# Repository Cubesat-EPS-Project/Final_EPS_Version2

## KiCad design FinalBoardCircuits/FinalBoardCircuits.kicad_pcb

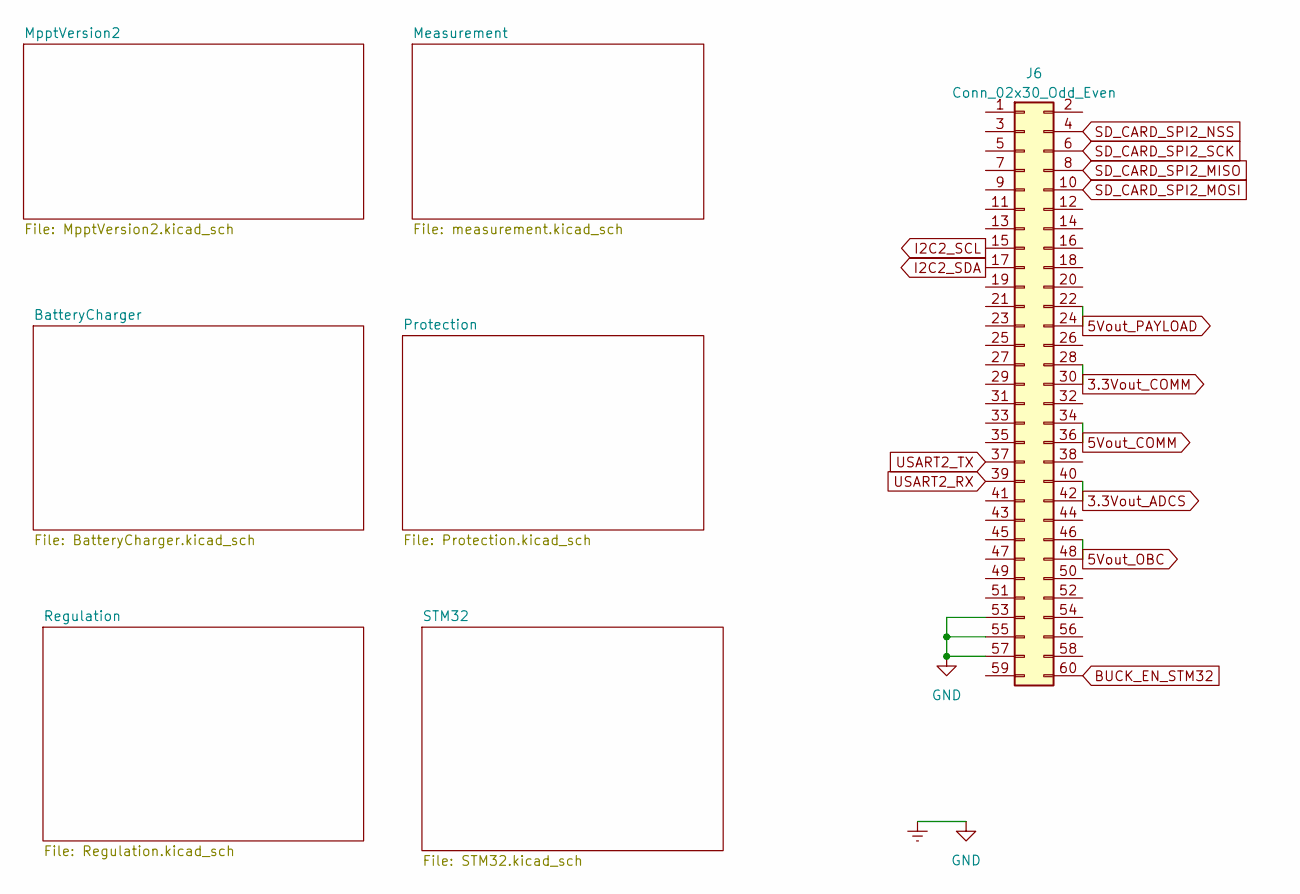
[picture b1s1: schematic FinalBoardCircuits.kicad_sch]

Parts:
J6: Conn_02x30_Odd_Even; PinSocket_2x30_P2.54mm_Vertical

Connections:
3.3Vout_ADCS: J6.40, J6.42; also elsewhere on the board
3.3Vout_COMM: J6.28, J6.30; also elsewhere on the board
5Vout_COMM: J6.34, J6.36; also elsewhere on the board
5Vout_OBC: J6.46, J6.48; also elsewhere on the board
5Vout_PAYLOAD: J6.22, J6.24; also elsewhere on the board
BUCK_EN_STM32: J6.60; also elsewhere on the board
I2C2_SCL: J6.15; also elsewhere on the board
I2C2_SDA: J6.17; also elsewhere on the board
SD_CARD_SPI2_MISO: J6.8; also elsewhere on the board
SD_CARD_SPI2_MOSI: J6.10; also elsewhere on the board
SD_CARD_SPI2_NSS: J6.4; also elsewhere on the board
SD_CARD_SPI2_SCK: J6.6; also elsewhere on the board
USART2_RX: J6.39; also elsewhere on the board
USART2_TX: J6.37; also elsewhere on the board

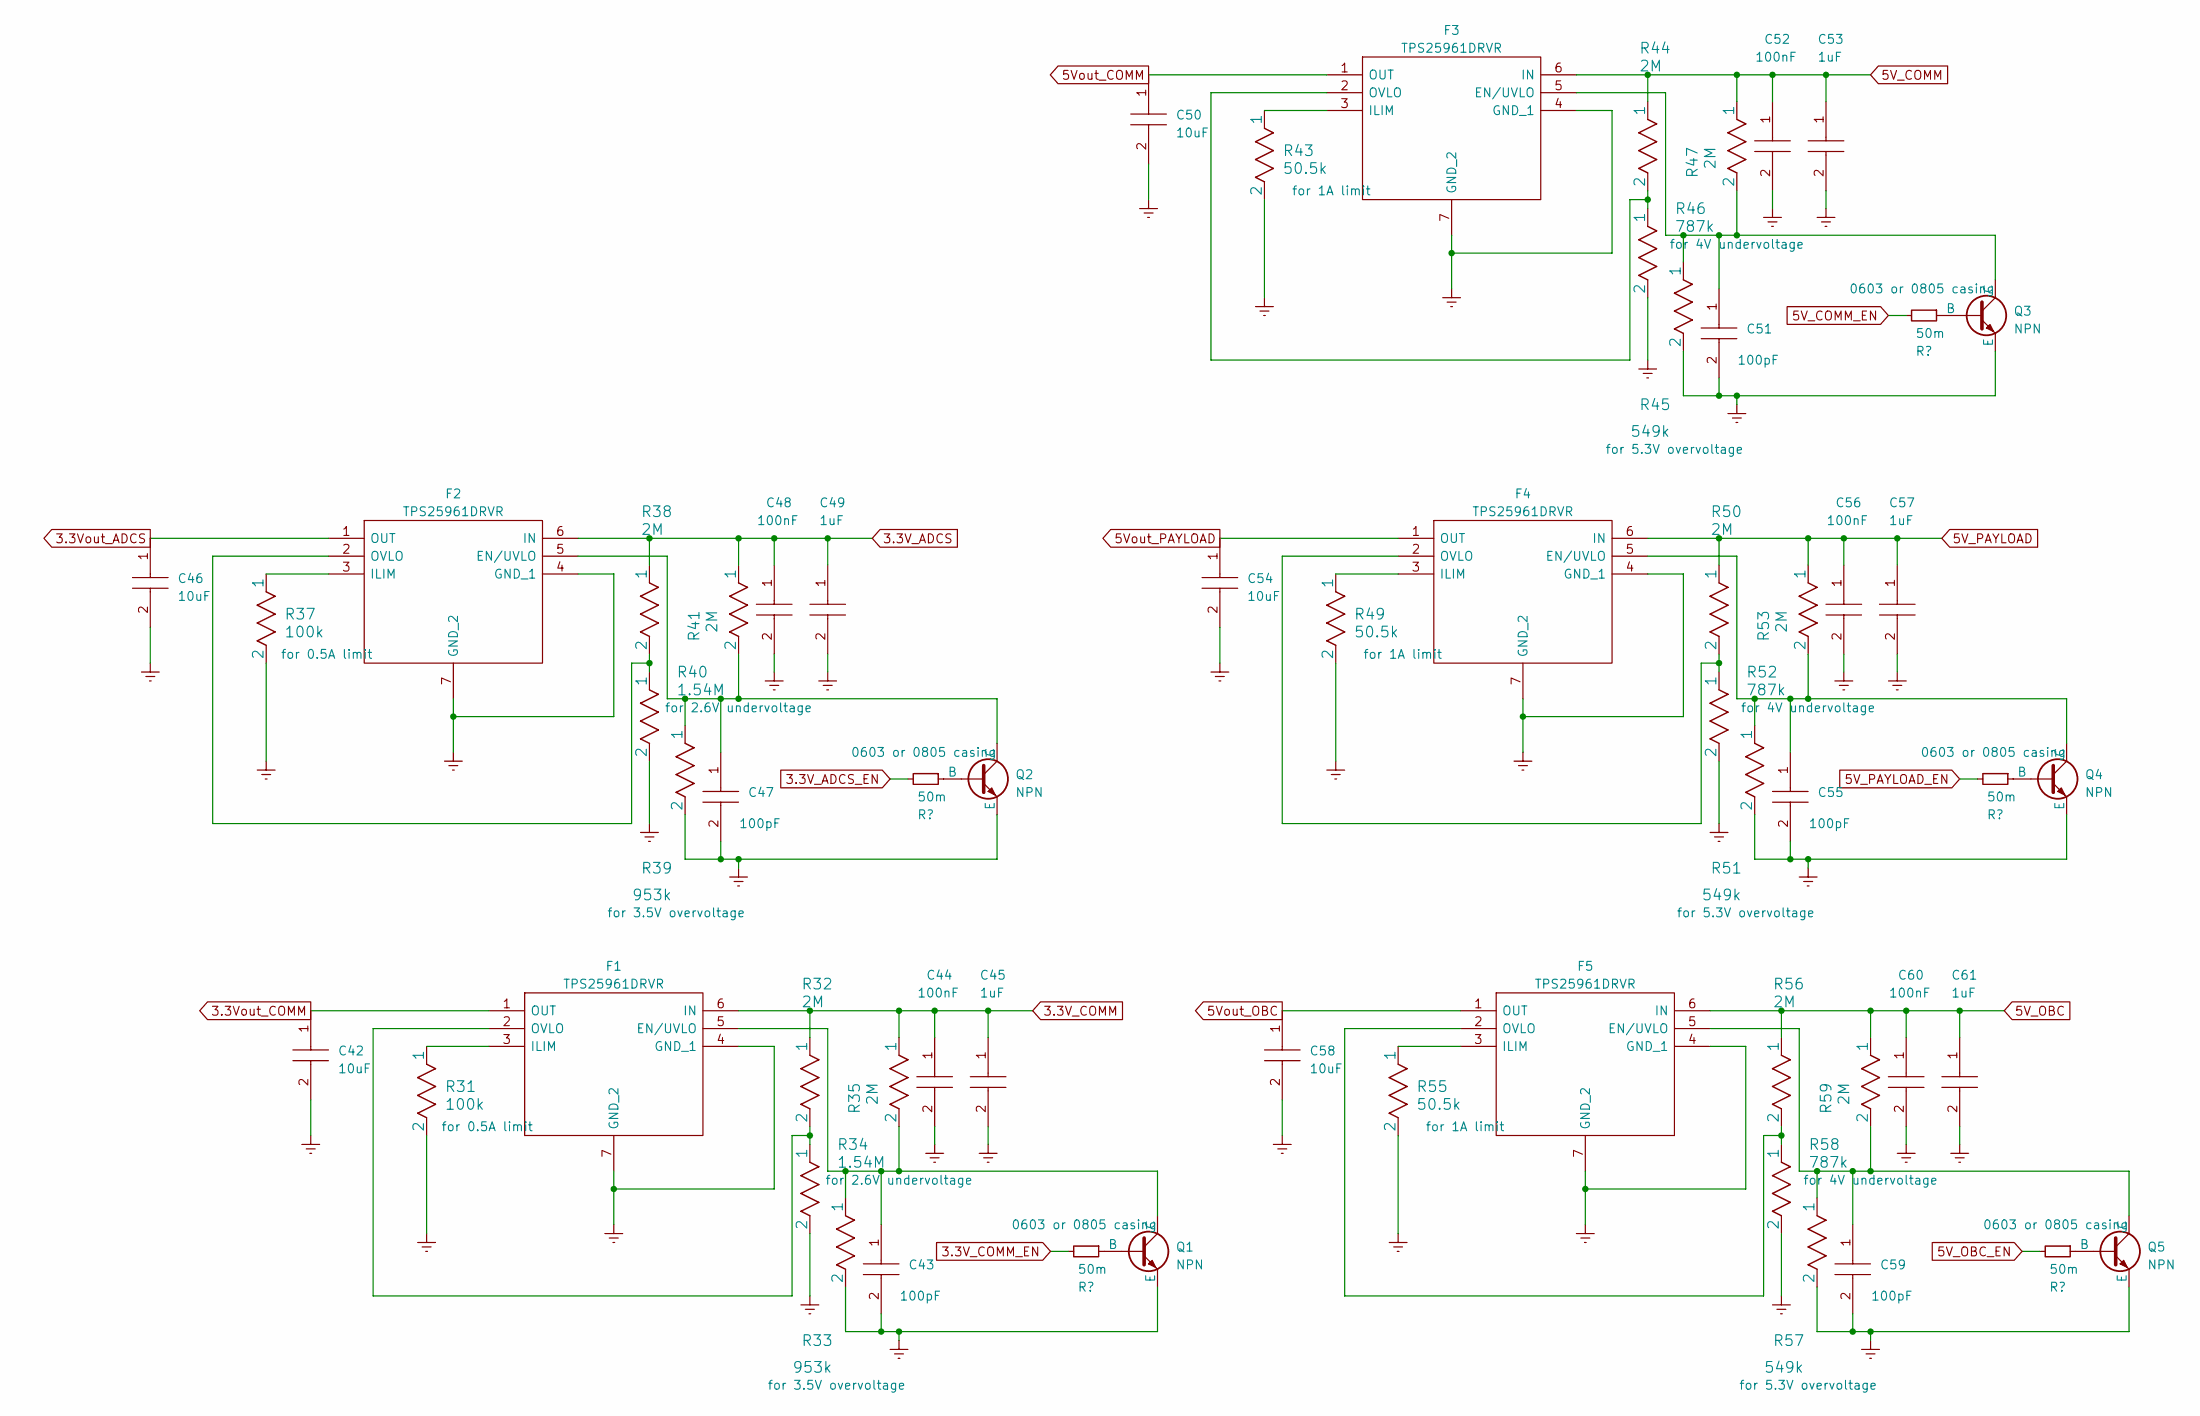
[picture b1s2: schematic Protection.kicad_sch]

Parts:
C42, C46, C50, C54, C58: 10uF; C_0805_2012Metric_Pad1.18x1.45mm_HandSolder; Mouser Part Number 581-0805YC106KAT2A
C43, C47, C51, C55, C59: 100pF; C_0805_2012Metric_Pad1.18x1.45mm_HandSolder; Mouser Part Number 80-C0402C101K3RAUTO
C44, C48, C52, C56, C60: 100nF; C_0805_2012Metric_Pad1.18x1.45mm_HandSolder; Mouser Part Number 810-C1005X7R1C104K
C45, C49, C53, C57, C61: 1uF; C_0805_2012Metric_Pad1.18x1.45mm_HandSolder; Mouser Part Number 80-C2220X105K2RAUTO
F1, F2, F3, F4, F5: TPS25961DRVR; SON65P200X200X80-7N; Mouser Part Number 595-TPS25961DRVR
Q1, Q2, Q3, Q4, Q5: NPN; PBSS4310PASQX
R31, R37: 100k; R_0805_2012Metric_Pad1.20x1.40mm_HandSolder
R32, R35, R38, R41, R44, R47, R50, R53, R56, R59: 2M; R_0805_2012Metric_Pad1.20x1.40mm_HandSolder
R33, R39: 953k; R_0805_2012Metric_Pad1.20x1.40mm_HandSolder
R34, R40: 1.54M; R_0805_2012Metric_Pad1.20x1.40mm_HandSolder
R36, R42, R48, R54, R60: 50m; R_0805_2012Metric_Pad1.20x1.40mm_HandSolder
R43, R49, R55: 50.5k; R_0805_2012Metric_Pad1.20x1.40mm_HandSolder
R45, R51, R57: 549k; R_0805_2012Metric_Pad1.20x1.40mm_HandSolder
R46, R52, R58: 787k; R_0805_2012Metric_Pad1.20x1.40mm_HandSolder

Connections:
3.3V_ADCS: C48.1, C49.1, F2.6 (IN), R38.1, R41.1; also elsewhere on the board
3.3V_ADCS_EN: R42.2; also elsewhere on the board
3.3V_COMM: C44.1, C45.1, F1.6 (IN), R32.1, R35.1; also elsewhere on the board
3.3V_COMM_EN: R36.2; also elsewhere on the board
3.3Vout_ADCS: C46.1, F2.1 (OUT); also elsewhere on the board
3.3Vout_COMM: C42.1, F1.1 (OUT); also elsewhere on the board
5V_COMM: C52.1, C53.1, F3.6 (IN), R44.1, R47.1; also elsewhere on the board
5V_COMM_EN: R48.2; also elsewhere on the board
5V_OBC: C60.1, C61.1, F5.6 (IN), R56.1, R59.1; also elsewhere on the board
5V_OBC_EN: R60.2; also elsewhere on the board
5V_PAYLOAD: C56.1, C57.1, F4.6 (IN), R50.1, R53.1; also elsewhere on the board
5V_PAYLOAD_EN: R54.2; also elsewhere on the board
5Vout_COMM: C50.1, F3.1 (OUT); also elsewhere on the board
5Vout_OBC: C58.1, F5.1 (OUT); also elsewhere on the board
5Vout_PAYLOAD: C54.1, F4.1 (OUT); also elsewhere on the board
unnamed: C43.1, F1.5 (EN/UVLO), Q1.1 (C), R34.1, R35.2
unnamed: F1.3 (ILIM), R31.1
unnamed: F1.2 (OVLO), R32.2, R33.1
unnamed: C47.1, F2.5 (EN/UVLO), Q2.1 (C), R40.1, R41.2
unnamed: F2.3 (ILIM), R37.1
unnamed: F2.2 (OVLO), R38.2, R39.1
unnamed: C51.1, F3.5 (EN/UVLO), Q3.1 (C), R46.1, R47.2
unnamed: F3.3 (ILIM), R43.1
unnamed: F3.2 (OVLO), R44.2, R45.1
unnamed: C55.1, F4.5 (EN/UVLO), Q4.1 (C), R52.1, R53.2
unnamed: F4.3 (ILIM), R49.1
unnamed: F4.2 (OVLO), R50.2, R51.1
unnamed: C59.1, F5.5 (EN/UVLO), Q5.1 (C), R58.1, R59.2
unnamed: F5.3 (ILIM), R55.1
unnamed: F5.2 (OVLO), R56.2, R57.1
unnamed: Q1.2 (B), R36.1
unnamed: Q2.2 (B), R42.1
unnamed: Q3.2 (B), R48.1
unnamed: Q4.2 (B), R54.1
unnamed: Q5.2 (B), R60.1

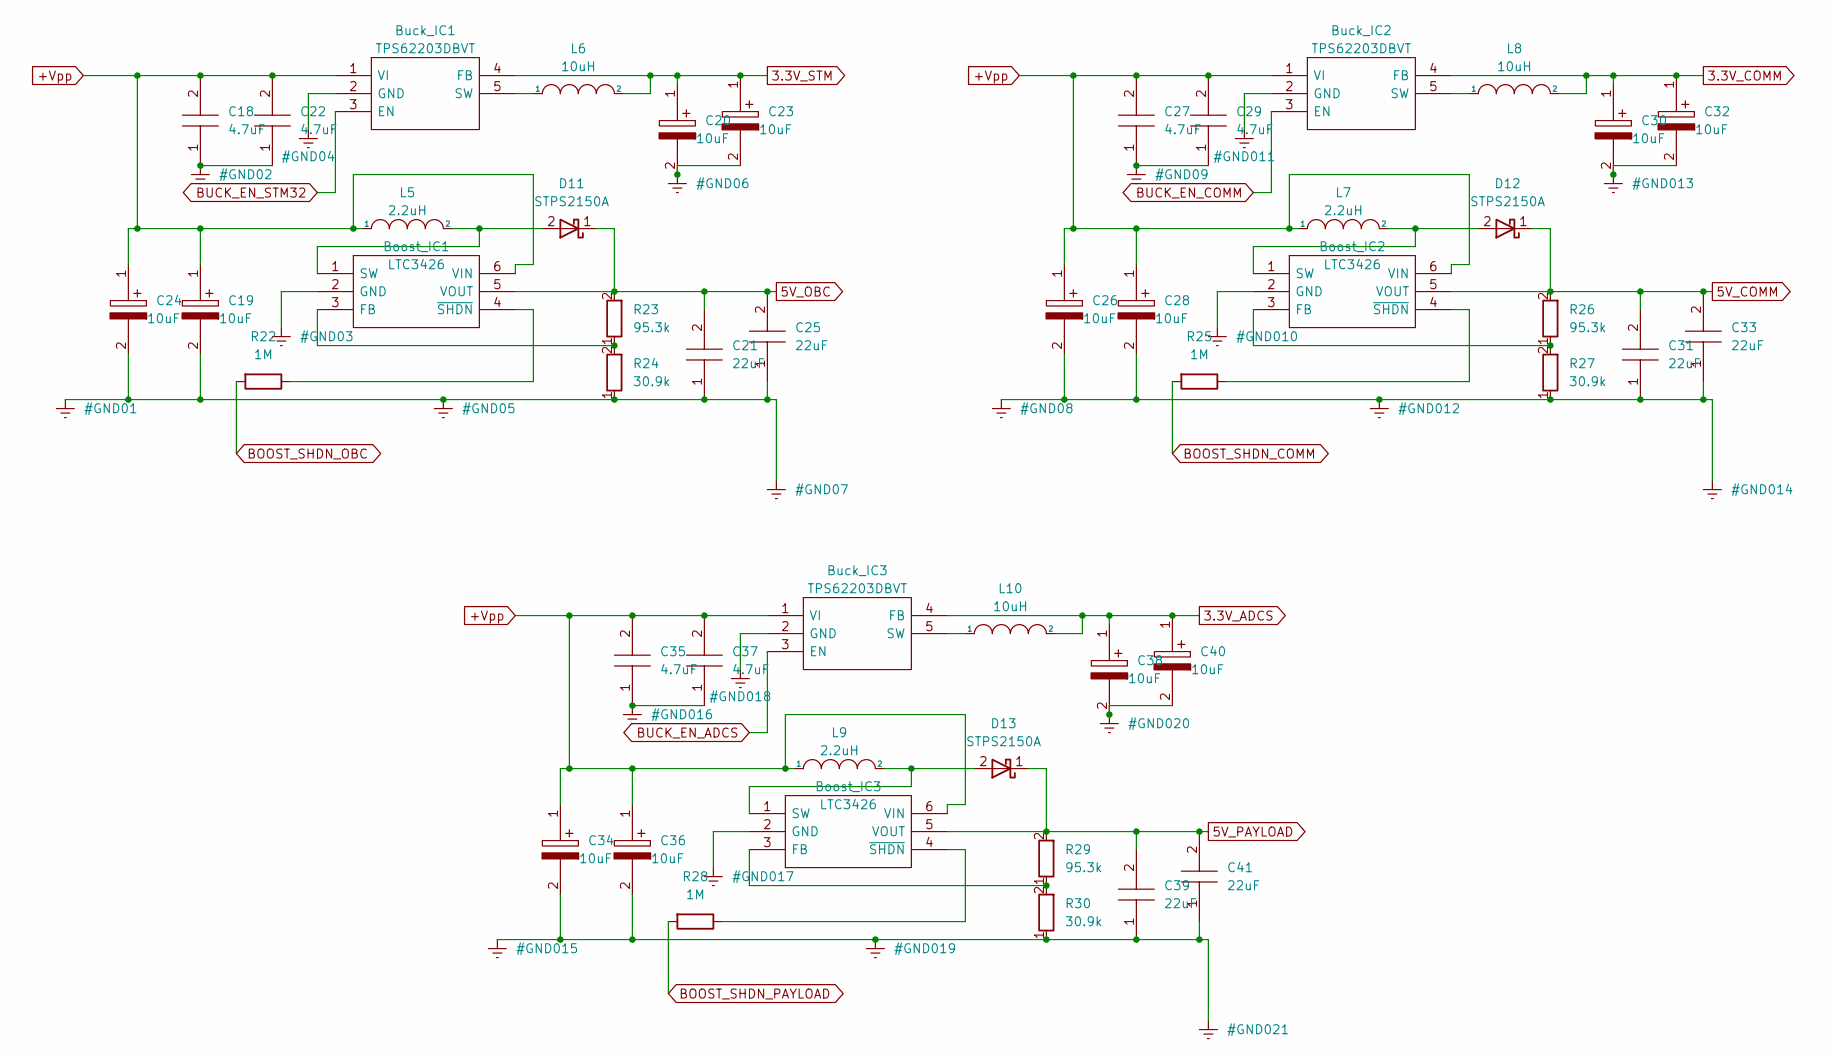
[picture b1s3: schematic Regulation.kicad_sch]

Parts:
Boost_IC1, Boost_IC2, Boost_IC3: LTC3426; SOT95P280X90-6N; Mouser Part Number 584-LTC3426ES6TRMPBF
Buck_IC1, Buck_IC2, Buck_IC3: TPS62203DBVT; SOT95P280X145-5N; Mouser Part Number 595-TPS62203DBVT
C18, C22, C27, C29, C35, C37: 4.7uF; C_0805_2012Metric_Pad1.18x1.45mm_HandSolder; Mouser Part Number 80-C1210C475K4RAUTO
C19, C20, C23, C24, C26, C28, C30, C32, C34, C36, C38, C40: 10uF; C_0805_2012Metric_Pad1.18x1.45mm_HandSolder; Mouser Part Number 598-AFK106M35C12T-F
C21, C25, C31, C33, C39, C41: 22uF; C_0805_2012Metric_Pad1.18x1.45mm_HandSolder; Mouser Part Number 81-ZRB18AR61A226ME1L
D11, D12, D13: STPS2150A
L5, L7, L9: 2.2uH; L_0805_2012Metric_Pad1.05x1.20mm_HandSolder
L6, L8, L10: 10uH; B82442T1103K050
R22, R25, R28: 1M; R_0805_2012Metric_Pad1.20x1.40mm_HandSolder
R23, R26, R29: 95.3k; R_0805_2012Metric_Pad1.20x1.40mm_HandSolder
R24, R27, R30: 30.9k; R_0805_2012Metric_Pad1.20x1.40mm_HandSolder

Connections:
3.3V_ADCS: Buck_IC3.4 (FB), C38.1, C40.1, L10.2; also elsewhere on the board
3.3V_COMM: Buck_IC2.4 (FB), C30.1, C32.1, L8.2; also elsewhere on the board
3.3V_STM: Buck_IC1.4 (FB), C20.1, C23.1, L6.2; also elsewhere on the board
5V_COMM: Boost_IC2.5 (VOUT), C31.2, C33.2, D12.1 (K), R26.2; also elsewhere on the board
5V_OBC: Boost_IC1.5 (VOUT), C21.2, C25.2, D11.1 (K), R23.2; also elsewhere on the board
5V_PAYLOAD: Boost_IC3.5 (VOUT), C39.2, C41.2, D13.1 (K), R29.2; also elsewhere on the board
+Vpp: Boost_IC1.6 (VIN), Boost_IC2.6 (VIN), Boost_IC3.6 (VIN), Buck_IC1.1 (VI), Buck_IC2.1 (VI), Buck_IC3.1 (VI), C18.2, C19.1, C22.2, C24.1, C26.1, C27.2, C28.1, C29.2, C34.1, C35.2, C36.1, C37.2, L5.1, L7.1, L9.1; also elsewhere on the board
BOOST_SHDN_COMM: R25.2; also elsewhere on the board
BOOST_SHDN_OBC: R22.2; also elsewhere on the board
BOOST_SHDN_PAYLOAD: R28.2; also elsewhere on the board
BUCK_EN_ADCS: Buck_IC3.3 (EN); also elsewhere on the board
BUCK_EN_COMM: Buck_IC2.3 (EN); also elsewhere on the board
BUCK_EN_STM32: Buck_IC1.3 (EN); also elsewhere on the board
unnamed: Boost_IC1.3 (FB), R23.1, R24.2
unnamed: Boost_IC1.1 (SW), D11.2 (A), L5.2
unnamed: Boost_IC1.4 (~SHDN), R22.1
unnamed: Boost_IC2.3 (FB), R26.1, R27.2
unnamed: Boost_IC2.1 (SW), D12.2 (A), L7.2
unnamed: Boost_IC2.4 (~SHDN), R25.1
unnamed: Boost_IC3.3 (FB), R29.1, R30.2
unnamed: Boost_IC3.1 (SW), D13.2 (A), L9.2
unnamed: Boost_IC3.4 (~SHDN), R28.1
unnamed: Buck_IC1.5 (SW), L6.1
unnamed: Buck_IC2.5 (SW), L8.1
unnamed: Buck_IC3.5 (SW), L10.1

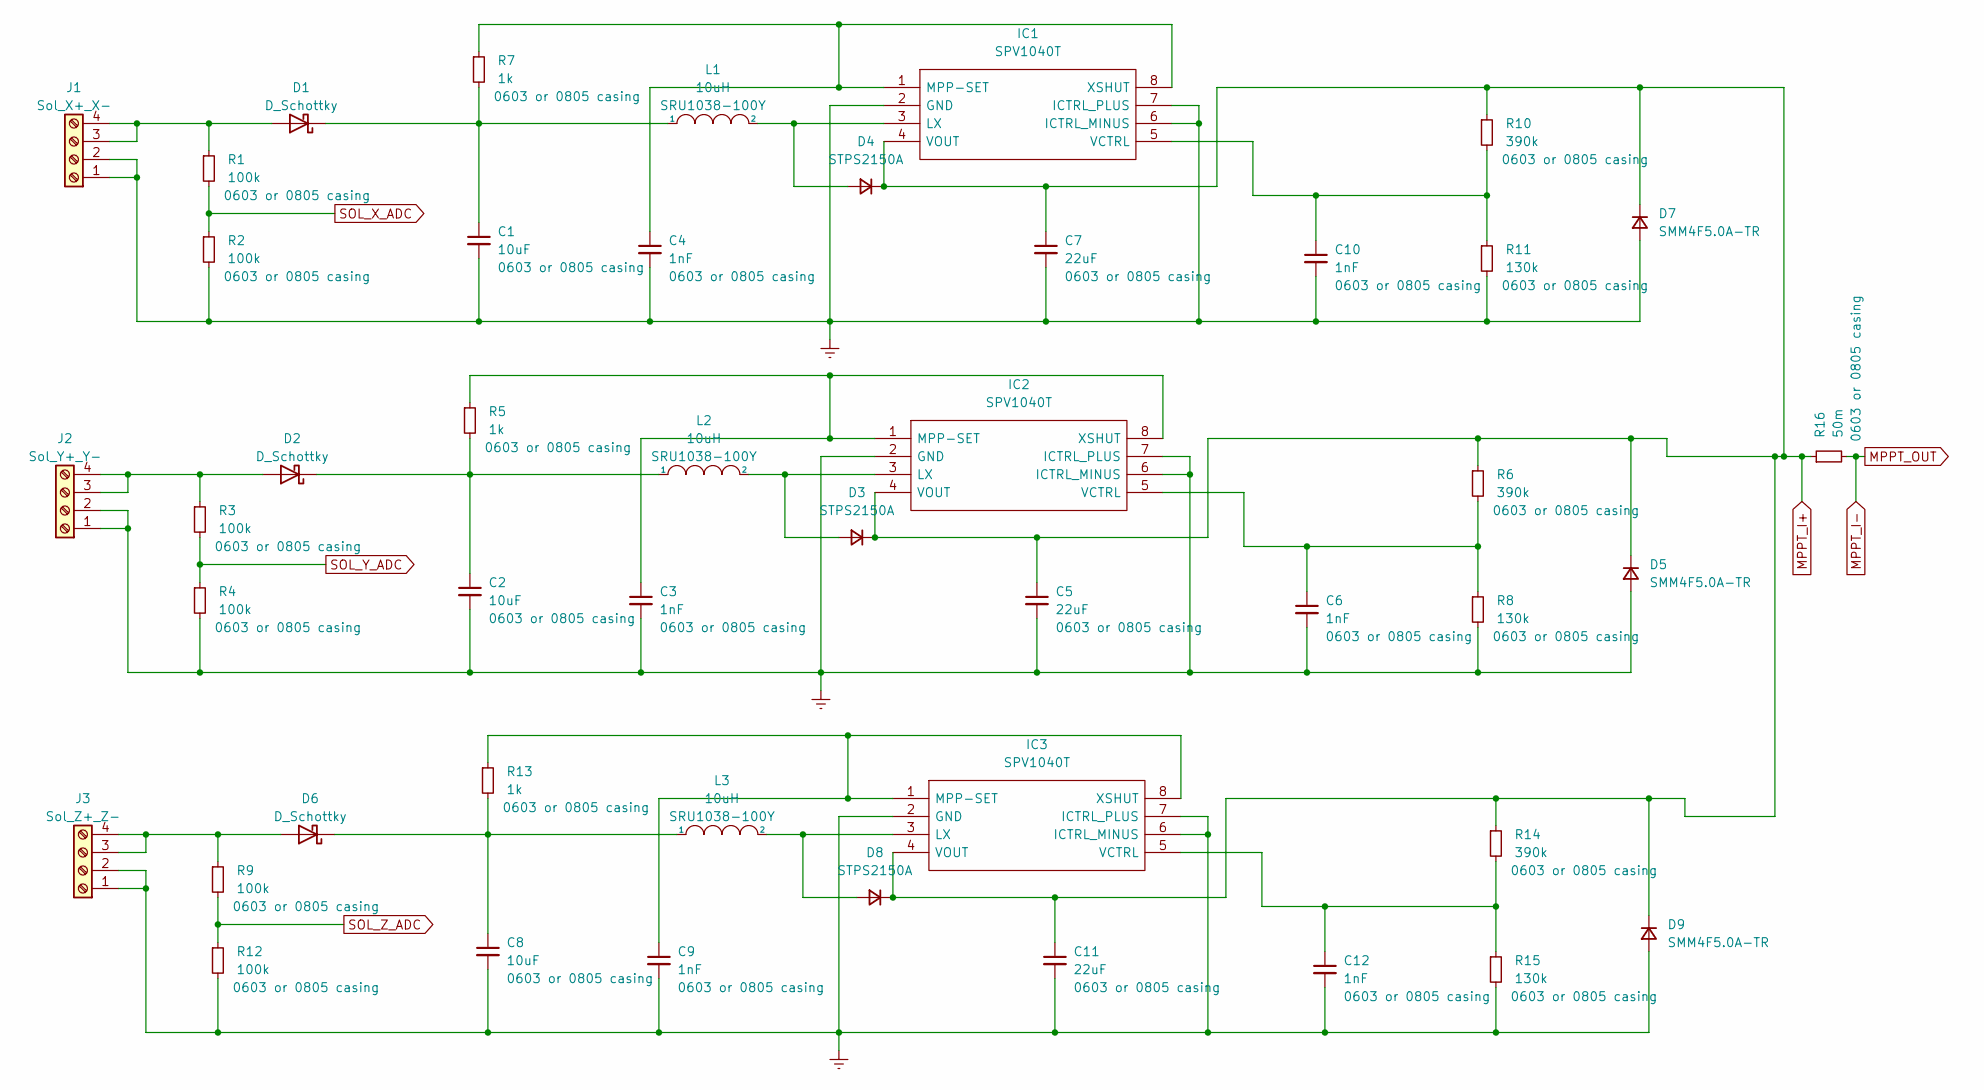
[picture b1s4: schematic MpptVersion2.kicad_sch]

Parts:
C1, C2, C8: 10uF; C_0805_2012Metric_Pad1.18x1.45mm_HandSolder
C3, C4, C6, C9, C10, C12: 1nF; C_0805_2012Metric_Pad1.18x1.45mm_HandSolder
C5, C7, C11: 22uF; C_0805_2012Metric_Pad1.18x1.45mm_HandSolder
D1, D2, D6: D_Schottky; STPS2150A
D3, D4, D8: STPS2150A
D5, D7, D9: SMM4F5.0A-TR
IC1, IC2, IC3: SPV1040T; Mouser Part Number 511-SPV1040T
J1: Sol_X+_X-; JST_GH_SM04B-GHS-TB_1x04-1MP_P1.25mm_Horizontal
J2: Sol_Y+_Y-; JST_GH_SM04B-GHS-TB_1x04-1MP_P1.25mm_Horizontal
J3: Sol_Z+_Z-; JST_GH_SM04B-GHS-TB_1x04-1MP_P1.25mm_Horizontal
L1, L2, L3: 10uH; B82442T1103K050
R1, R2, R3, R4, R9, R12: 100k; R_0805_2012Metric_Pad1.20x1.40mm_HandSolder
R5, R7, R13: 1k; R_0805_2012Metric_Pad1.20x1.40mm_HandSolder
R6, R10, R14: 390k; R_0805_2012Metric_Pad1.20x1.40mm_HandSolder
R8, R11, R15: 130k; R_0805_2012Metric_Pad1.20x1.40mm_HandSolder
R16: 50m; R_0805_2012Metric_Pad1.20x1.40mm_HandSolder

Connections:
MPPT_I+: C5.1, C7.1, C11.1, D3.1 (K), D4.1 (K), D5.1 (K), D5.3, D7.1 (K), D7.3, D8.1 (K), D9.1 (K), D9.3, IC1.4 (VOUT), IC2.4 (VOUT), IC3.4 (VOUT), R6.1, R10.1, R14.1, R16.1; also elsewhere on the board
MPPT_I-: R16.2; also elsewhere on the board
unnamed: C1.1, D1.1 (K), L1.1, R7.2
unnamed: D2.2 (A), J2.3, J2.4, R3.1
unnamed: C2.1, D2.1 (K), L2.1, R5.2
unnamed: D3.2 (A), IC2.3 (LX), L2.2
unnamed: D4.2 (A), IC1.3 (LX), L1.2
unnamed: D6.2 (A), J3.3, J3.4, R9.1
unnamed: C8.1, D6.1 (K), L3.1, R13.2
unnamed: D8.2 (A), IC3.3 (LX), L3.2
unnamed: C10.1, IC1.5 (VCTRL), R10.2, R11.1
unnamed: C3.1, IC2.1 (MPP-SET), IC2.8 (XSHUT), R5.1
unnamed: C6.1, IC2.5 (VCTRL), R6.2, R8.1
unnamed: C9.1, IC3.1 (MPP-SET), IC3.8 (XSHUT), R13.1
unnamed: C12.1, IC3.5 (VCTRL), R14.2, R15.1
SOL_Y_ADC: R3.2, R4.1; also elsewhere on the board
SOL_Z_ADC: R9.2, R12.1; also elsewhere on the board

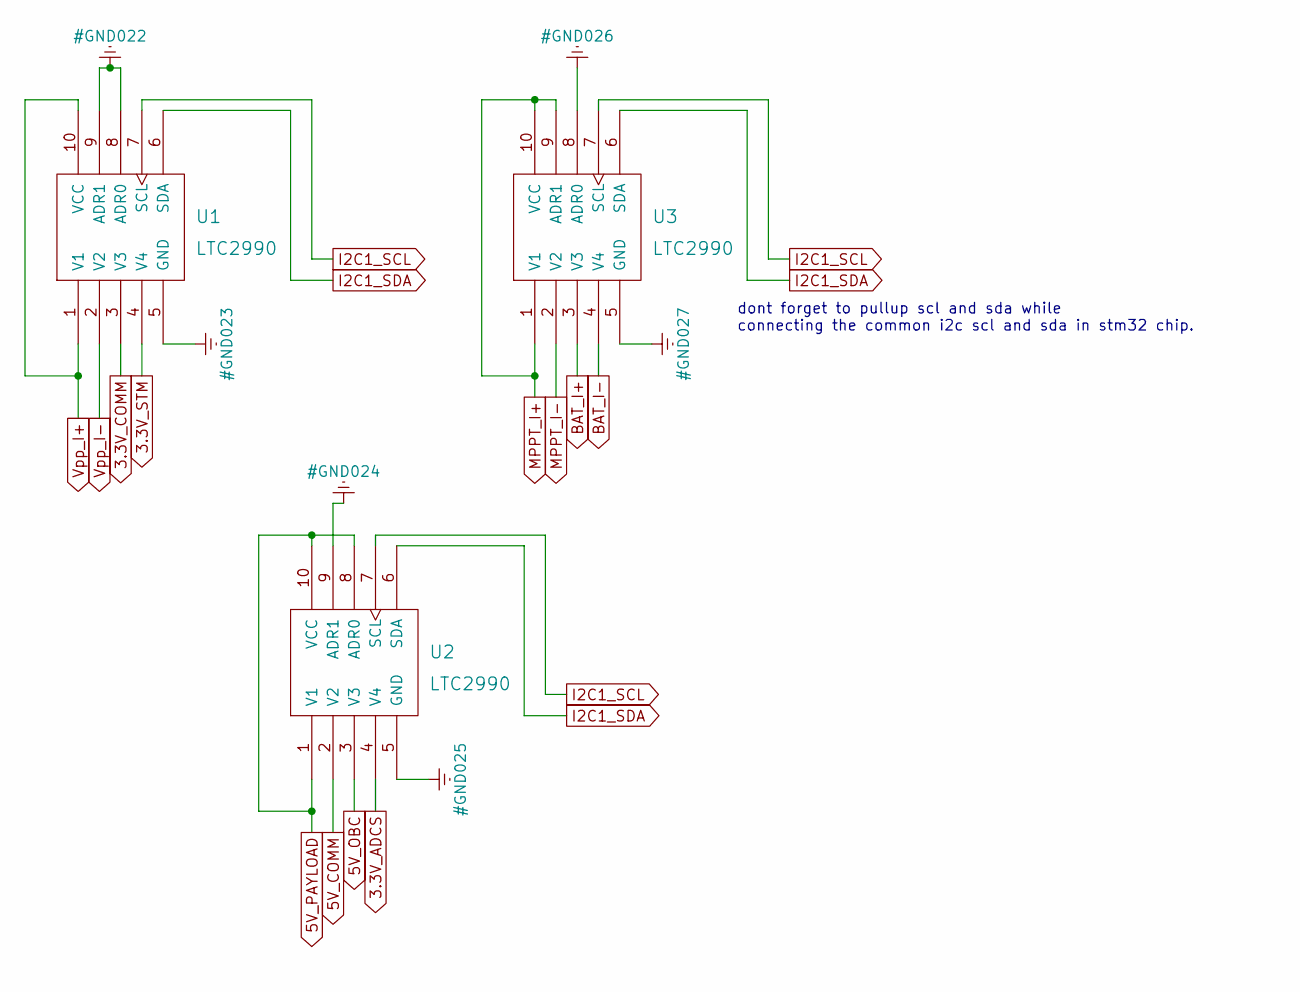
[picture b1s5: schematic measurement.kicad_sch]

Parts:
U1, U2, U3: LTC2990; SOP50P490X110-10N

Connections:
3.3V_ADCS: U2.4 (V4); also elsewhere on the board
3.3V_COMM: U1.3 (V3); also elsewhere on the board
3.3V_STM: U1.4 (V4); also elsewhere on the board
5V_COMM: U2.2 (V2); also elsewhere on the board
5V_OBC: U2.3 (V3); also elsewhere on the board
5V_PAYLOAD: U2.1 (V1), U2.8 (ADR0), U2.10 (VCC); also elsewhere on the board
+Vpp: U1.2 (V2); also elsewhere on the board
BAT_I+: U3.3 (V3); also elsewhere on the board
I2C1_SCL: U1.7 (SCL), U2.7 (SCL), U3.7 (SCL); also elsewhere on the board
I2C1_SDA: U1.6 (SDA), U2.6 (SDA), U3.6 (SDA); also elsewhere on the board
MPPT_I+: U3.1 (V1), U3.9 (ADR1), U3.10 (VCC); also elsewhere on the board
MPPT_I-: U3.2 (V2); also elsewhere on the board
Vpp_I+: U1.1 (V1), U1.10 (VCC)

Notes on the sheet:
dont forget to pullup scl and sda while connecting the common i2c scl and sda in stm32 chip.

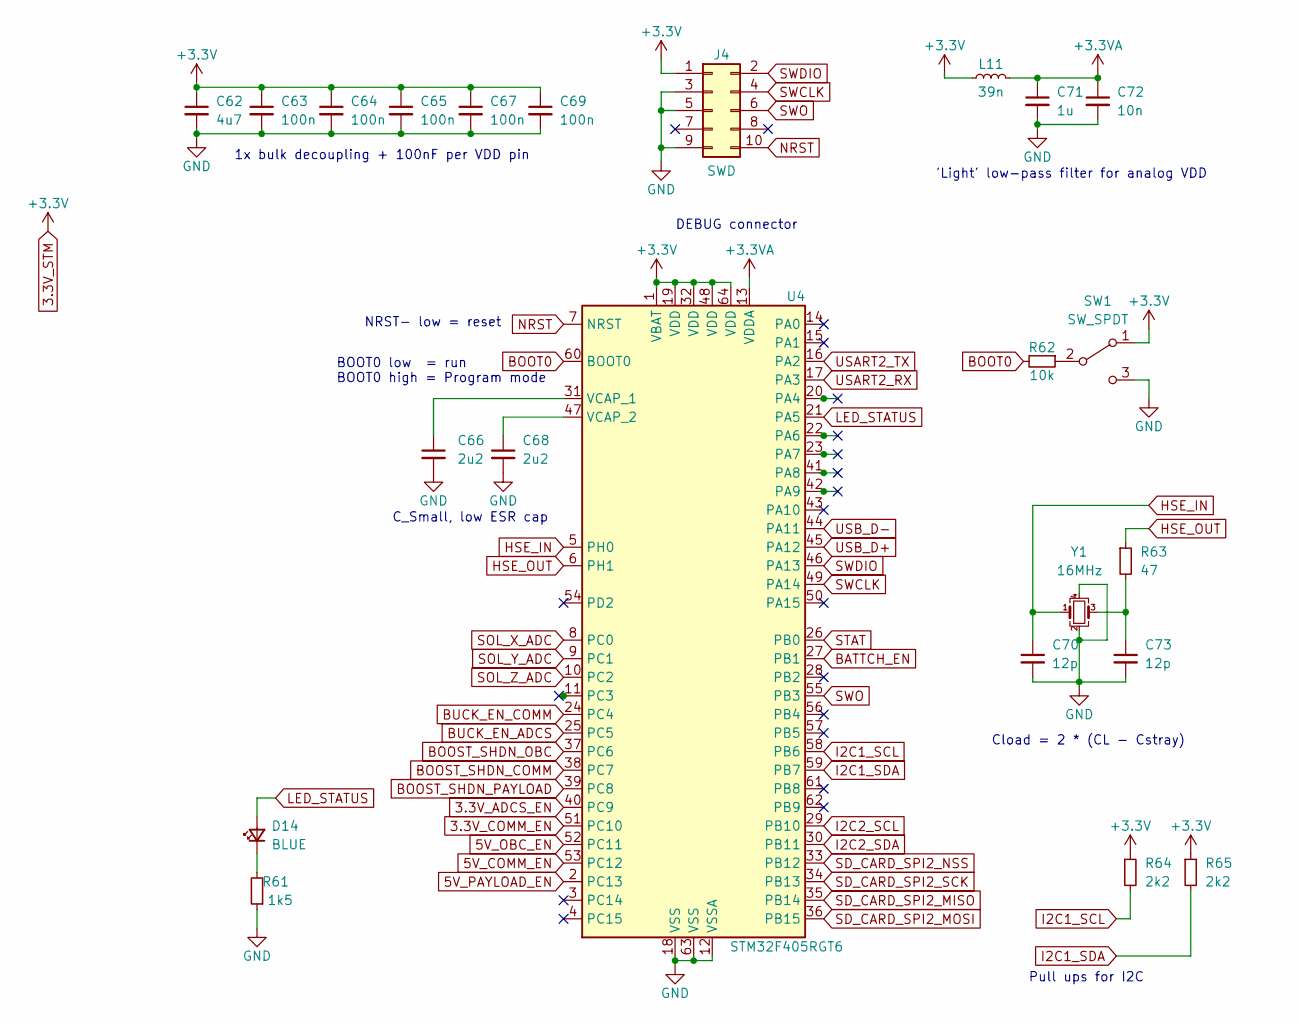
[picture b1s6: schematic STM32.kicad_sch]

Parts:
C62: 4u7; C_0805_2012Metric_Pad1.18x1.45mm_HandSolder; LCSC Part # C19666
C63, C64, C65, C67, C69: 100n; C_0805_2012Metric_Pad1.18x1.45mm_HandSolder; LCSC Part # C1525
C66, C68: 2u2; C_0805_2012Metric_Pad1.18x1.45mm_HandSolder; LCSC Part # C23630
C70, C73: 12p; C_0805_2012Metric_Pad1.18x1.45mm_HandSolder; LCSC Part # C1547
C71: 1u; C_0805_2012Metric_Pad1.18x1.45mm_HandSolder; LCSC Part # C52923
C72: 10n; C_0805_2012Metric_Pad1.18x1.45mm_HandSolder; LCSC Part # C15195
D14: BLUE; LED_0805_2012Metric_Pad1.15x1.40mm_HandSolder; LCSC Part # C72041
J4: SWD; PinHeader_2x05_P1.00mm_Vertical_SMD
L11: 39n; L_0805_2012Metric_Pad1.15x1.40mm_HandSolder; LCSC Part # C26443
R61: 1k5; R_0805_2012Metric_Pad1.20x1.40mm_HandSolder; LCSC Part # C22843
R62: 10k; R_0805_2012Metric_Pad1.20x1.40mm_HandSolder; LCSC Part # C25744
R63: 47; R_0805_2012Metric_Pad1.20x1.40mm_HandSolder; LCSC Part # C25118
R64, R65: 2k2; R_0805_2012Metric_Pad1.20x1.40mm_HandSolder; LCSC Part # C25879
SW1: SW_SPDT; SW_SPDT_PCM12
U4: STM32F405RGT6; LQFP-64_10x10mm_P0.5mm; LCSC Part # C15742
Y1: 16MHz; Crystal_SMD_3225-4Pin_3.2x2.5mm; LCSC Part # C13738

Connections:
3.3V_ADCS_EN: U4.40 (PC9); also elsewhere on the board
3.3V_COMM_EN: U4.51 (PC10); also elsewhere on the board
3.3V_STM: C62.1, C63.1, C64.1, C65.1, C67.1, C69.1, J4.1, L11.1, R64.1, R65.1, SW1.1 (A), U4.1 (VBAT), U4.19 (VDD), U4.32 (VDD), U4.48 (VDD), U4.64 (VDD); also elsewhere on the board
5V_COMM_EN: U4.53 (PC12); also elsewhere on the board
5V_OBC_EN: U4.52 (PC11); also elsewhere on the board
5V_PAYLOAD_EN: U4.2 (PC13); also elsewhere on the board
+3.3VA: C71.1, C72.1, L11.2, U4.13 (VDDA)
BATTCH_EN: U4.27 (PB1); also elsewhere on the board
BOOST_SHDN_COMM: U4.38 (PC7); also elsewhere on the board
BOOST_SHDN_OBC: U4.37 (PC6); also elsewhere on the board
BOOST_SHDN_PAYLOAD: U4.39 (PC8); also elsewhere on the board
BOOT0: R62.2, U4.60 (BOOT0)
BUCK_EN_ADCS: U4.25 (PC5); also elsewhere on the board
BUCK_EN_COMM: U4.24 (PC4); also elsewhere on the board
HSE_IN: C70.1, U4.5 (PH0), Y1.1
HSE_OUT: R63.1, U4.6 (PH1)
I2C1_SCL: R64.2, U4.58 (PB6); also elsewhere on the board
I2C1_SDA: R65.2, U4.59 (PB7); also elsewhere on the board
I2C2_SCL: U4.29 (PB10); also elsewhere on the board
I2C2_SDA: U4.30 (PB11); also elsewhere on the board
LED_STATUS: D14.2 (A), U4.21 (PA5)
NRST: J4.10, U4.7 (NRST)
unnamed: C73.1, R63.2, Y1.3
unnamed: D14.1 (K), R61.2
unnamed: R62.1, SW1.2 (B)
unnamed: C66.1, U4.31 (VCAP_1)
unnamed: C68.1, U4.47 (VCAP_2)
SD_CARD_SPI2_MISO: U4.35 (PB14); also elsewhere on the board
SD_CARD_SPI2_MOSI: U4.36 (PB15); also elsewhere on the board
SD_CARD_SPI2_NSS: U4.33 (PB12); also elsewhere on the board
SD_CARD_SPI2_SCK: U4.34 (PB13); also elsewhere on the board
SOL_Y_ADC: U4.9 (PC1); also elsewhere on the board
SOL_Z_ADC: U4.10 (PC2); also elsewhere on the board
STAT: U4.26 (PB0); also elsewhere on the board
SWCLK: J4.4, U4.49 (PA14)
SWDIO: J4.2, U4.46 (PA13)
SWO: J4.6, U4.55 (PB3)
USART2_RX: U4.17 (PA3); also elsewhere on the board
USART2_TX: U4.16 (PA2); also elsewhere on the board
USB_D+: U4.45 (PA12); also elsewhere on the board
USB_D-: U4.44 (PA11); also elsewhere on the board

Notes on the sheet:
BOOT0 low = run BOOT0 high = Program mode
NRST- low = reset
Cload = 2 * (CL - Cstray)
DEBUG connector
1x bulk decoupling + 100nF per VDD pin
Pull ups for I2C
'Light' low-pass filter for analog VDD
C_Small, low ESR cap

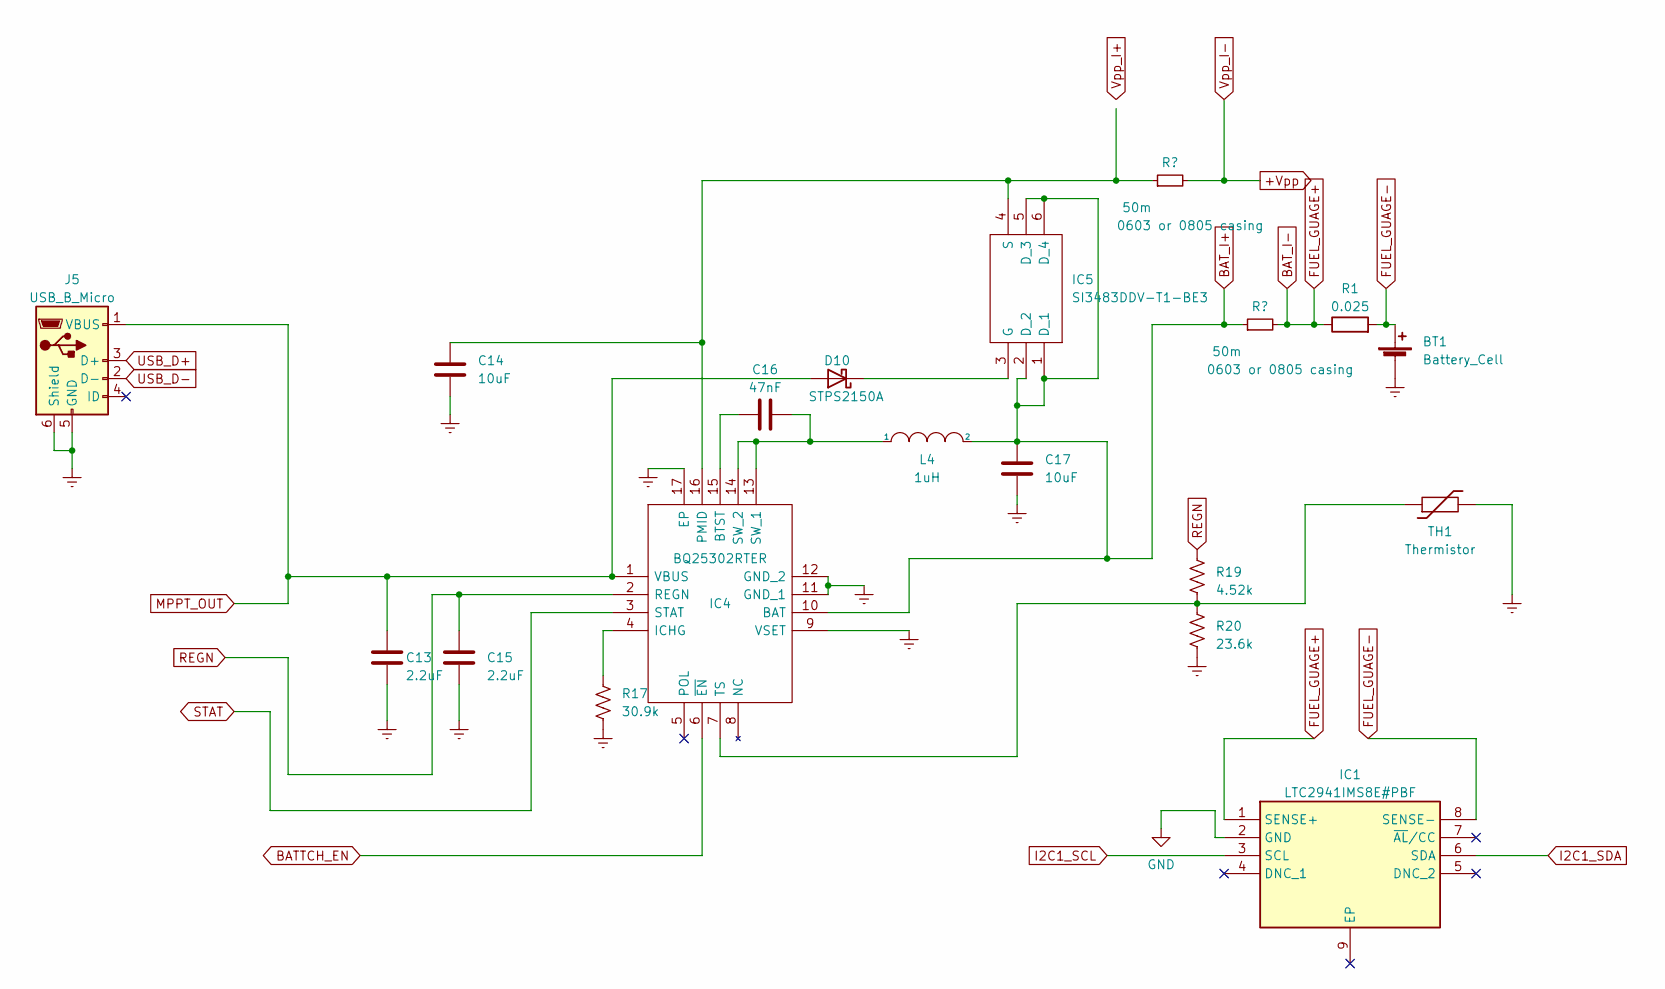
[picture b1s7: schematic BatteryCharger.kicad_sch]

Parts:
BT1: Battery_Cell; BatteryHolder_Keystone_1042_1x18650
C13, C15: 2.2uF; C_0805_2012Metric_Pad1.18x1.45mm_HandSolder
C14: 10uF; C_0805_2012Metric_Pad1.18x1.45mm_HandSolder
C16: 47nF; C_0805_2012Metric
C17: 10uF; C_0805_2012Metric
D10: STPS2150A
IC1: LTC2941IMS8E#PBF; SOP65P490X110-9N; Mouser Part Number 584-LTC2941IMS8E#PBF
IC4: BQ25302RTER; QFN50P300X300X80-17N-D; Mouser Part Number 595-BQ25302RTER
IC5: SI3483DDV-T1-BE3; SOT95P284X110-6N; Mouser Part Number 78-SI3483DDV-T1-BE3
J5: USB_B_Micro; USB_Micro-B_Amphenol_10118194_Horizontal
L4: 1uH; L_0805_2012Metric_Pad1.15x1.40mm_HandSolder
R1: 0.025; R_0805_2012Metric_Pad1.20x1.40mm_HandSolder
R17: 30.9k; R_0805_2012Metric_Pad1.20x1.40mm_HandSolder
R18, R21: 50m; R_0805_2012Metric_Pad1.20x1.40mm_HandSolder
R19: 4.52k; R_0805_2012Metric_Pad1.20x1.40mm_HandSolder
R20: 23.6k; R_0805_2012Metric_Pad1.20x1.40mm_HandSolder
TH1: Thermistor; 103AT2

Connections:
+Vpp: R18.2; also elsewhere on the board
BATTCH_EN: IC4.6 (~EN); also elsewhere on the board
BAT_I+: C17.1, IC4.10 (BAT), IC5.1 (D_1), IC5.2 (D_2), IC5.5 (D_3), IC5.6 (D_4), L4.2, R21.1; also elsewhere on the board
MPPT_I+: IC1.4 (VOUT); also elsewhere on the board
MPPT_I-: C13.1, D10.2 (A), IC4.1 (VBUS), J5.1 (VBUS); also elsewhere on the board
unnamed 54: IC1.3 (LX); also elsewhere on the board
unnamed: D10.1 (K), IC5.3 (G)
unnamed 75: IC1.5 (VCTRL); also elsewhere on the board
unnamed: C16.1, IC4.15 (BTST)
unnamed: IC4.4 (ICHG), R17.2
unnamed: C14.1, IC4.16 (PMID), IC5.4 (S), R18.1
unnamed: C16.2, IC4.13 (SW_1), IC4.14 (SW_2), L4.1
unnamed: IC4.7 (TS), R19.1, R20.2, TH1.1
REGN: C15.1, IC4.2 (REGN), R19.2
STAT: IC4.3 (STAT); also elsewhere on the board
USB_D+: J5.3 (D+); also elsewhere on the board
USB_D-: J5.2 (D-); also elsewhere on the board

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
